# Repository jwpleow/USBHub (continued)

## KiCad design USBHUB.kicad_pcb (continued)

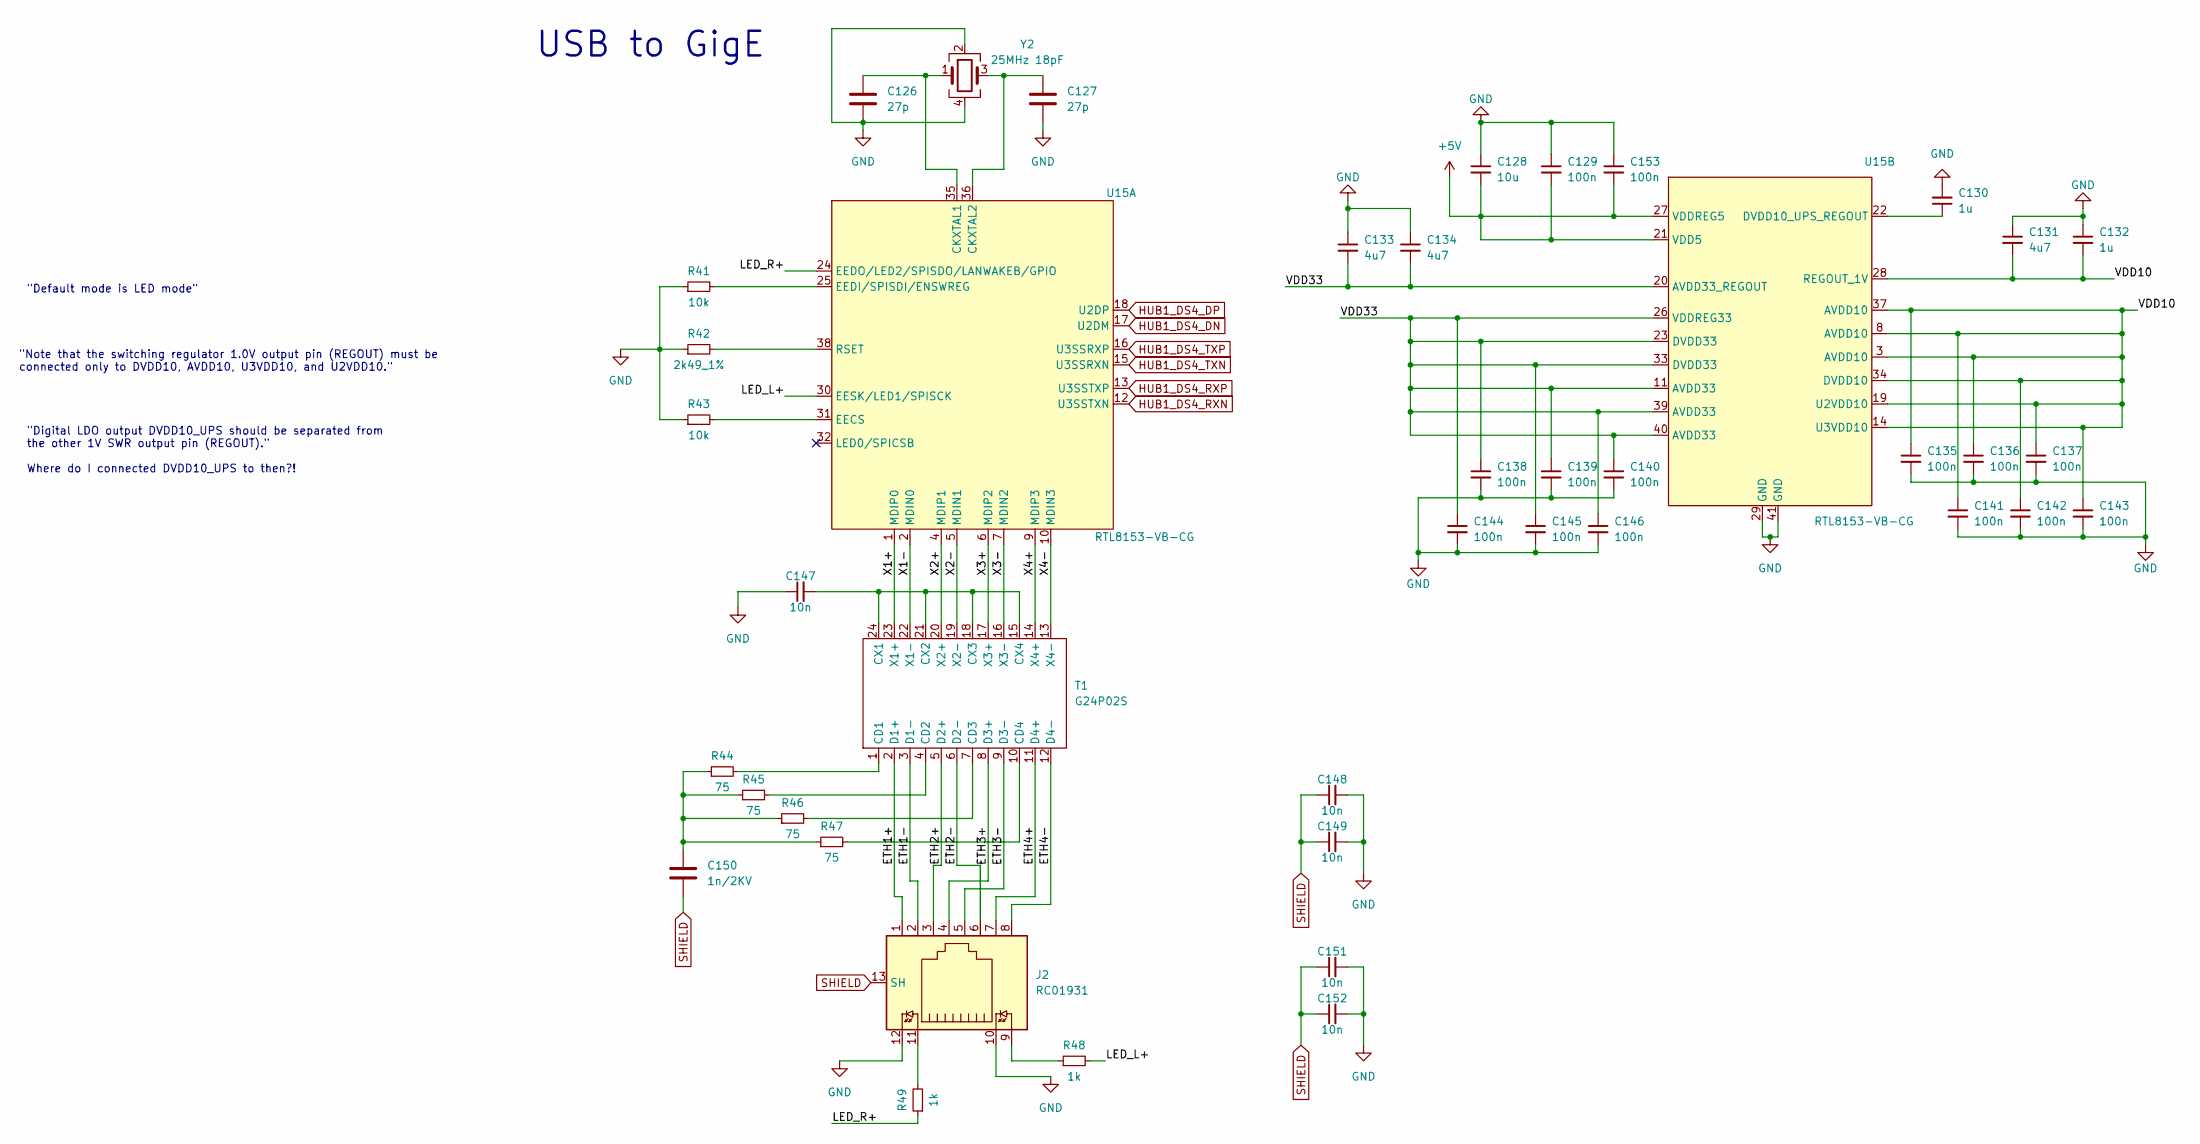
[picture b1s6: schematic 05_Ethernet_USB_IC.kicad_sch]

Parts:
C126, C127: 27p; C_0402_1005Metric
C128: 10u; C_0603_1608Metric
C129, C135, C136, C137, C138, C139, C140, C141, C142, C143, C144, C145, C146, C153: 100n; C_0402_1005Metric
C130, C132: 1u; C_0603_1608Metric
C131, C133, C134: 4u7; C_0603_1608Metric
C147, C148, C149, C151, C152: 10n; C_0402_1005Metric
C150: 1n/2KV; C_1206_3216Metric
J2: RC01931
R41, R43: 10k; R_0402_1005Metric
R42: 2k49_1%; R_0603_1608Metric
R44, R45, R46, R47: 75; R_0603_1608Metric
R48, R49: 1k; R_0603_1608Metric
T1: G24P02S
U15: RTL8153-VB-CG; RTL8153B-VB-CG
Y2: 25MHz 18pF; Crystal_SMD_2016-4Pin_2.0x1.6mm

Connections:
+5V: C128.2, C129.2, C153.2, U15.21 (VDD5), U15.27 (VDDREG5); also elsewhere on the board
/05 Ethernet USB IC/ETH1+: J2.1, T1.2 (D1+)
/05 Ethernet USB IC/ETH1-: J2.2, T1.3 (D1-)
/05 Ethernet USB IC/ETH2+: J2.3, T1.5 (D2+)
/05 Ethernet USB IC/ETH2-: J2.6, T1.6 (D2-)
/05 Ethernet USB IC/ETH3+: J2.4, T1.8 (D3+)
/05 Ethernet USB IC/ETH3-: J2.5, T1.9 (D3-)
/05 Ethernet USB IC/ETH4+: J2.7, T1.11 (D4+)
/05 Ethernet USB IC/ETH4-: J2.8, T1.12 (D4-)
/05 Ethernet USB IC/LED_L+: R48.2, U15.30 (EESK/LED1/SPISCK)
/05 Ethernet USB IC/LED_R+: R49.1, U15.24 (EEDO/LED2/SPISDO/LANWAKEB/GPIO)
/05 Ethernet USB IC/VDD10: C131.2, C132.2, C135.1, C136.1, C137.1, C141.1, C142.1, C143.1, U15.3 (AVDD10), U15.8 (AVDD10), U15.14 (U3VDD10), U15.19 (U2VDD10), U15.28 (REGOUT_1V), U15.34 (DVDD10), U15.37 (AVDD10)
/05 Ethernet USB IC/VDD33: C133.2, C134.2, C138.1, C139.1, C140.1, C144.1, C145.1, C146.1, U15.11 (AVDD33), U15.20 (AVDD33_REGOUT), U15.23 (DVDD33), U15.26 (VDDREG33), U15.33 (DVDD33), U15.39 (AVDD33), U15.40 (AVDD33)
/05 Ethernet USB IC/X1+: T1.23 (X1+), U15.1 (MDIP0)
/05 Ethernet USB IC/X1-: T1.22 (X1-), U15.2 (MDIN0)
/05 Ethernet USB IC/X2+: T1.20 (X2+), U15.4 (MDIP1)
/05 Ethernet USB IC/X2-: T1.19 (X2-), U15.5 (MDIN1)
/05 Ethernet USB IC/X3+: T1.17 (X3+), U15.6 (MDIP2)
/05 Ethernet USB IC/X3-: T1.16 (X3-), U15.7 (MDIN2)
/05 Ethernet USB IC/X4+: T1.14 (X4+), U15.9 (MDIP3)
/05 Ethernet USB IC/X4-: T1.13 (X4-), U15.10 (MDIN3)
GND: C126.2, C127.2, C128.1, C129.1, C130.2, C131.1, C132.1, C133.1, C134.1, C135.2, C136.2, C137.2, C138.2, C139.2, C140.2, C141.2, C142.2, C143.2, C144.2, C145.2, C146.2, C147.1, C148.2, C149.2, C151.2, C152.2, C153.1, J2.10, J2.12, R41.1, R42.1, R43.1, U15.29 (GND), U15.41 (GND), Y2.2, Y2.4; also elsewhere on the board
HUB1_DS4_DN: U15.17 (U2DM); also elsewhere on the board
HUB1_DS4_DP: U15.18 (U2DP); also elsewhere on the board
HUB1_DS4_RXN: U15.12 (U3SSTXN); also elsewhere on the board
HUB1_DS4_RXP: U15.13 (U3SSTXP); also elsewhere on the board
HUB1_DS4_TXN: U15.15 (U3SSRXN); also elsewhere on the board
HUB1_DS4_TXP: U15.16 (U3SSRXP); also elsewhere on the board
unnamed: C150.1, R44.1, R45.1, R46.1, R47.1
unnamed: J2.9, R48.1
unnamed: J2.11, R49.2
unnamed: R44.2, T1.1 (CD1)
unnamed: R45.2, T1.4 (CD2)
unnamed: R46.2, T1.7 (CD3)
unnamed: R47.2, T1.10 (CD4)
unnamed: C147.2, T1.15 (CX4), T1.18 (CX3), T1.21 (CX2), T1.24 (CX1)
unnamed: C126.1, U15.35 (CKXTAL1), Y2.1
unnamed: C127.1, U15.36 (CKXTAL2), Y2.3
unnamed: R43.2, U15.31 (EECS)
unnamed: R41.2, U15.25 (EEDI/SPISDI/ENSWREG)
unnamed: R42.2, U15.38 (RSET)
unnamed: C130.1, U15.22 (DVDD10_UPS_REGOUT)
SHIELD: C148.1, C149.1, C150.2, C151.1, C152.1, J2.13 (SH)

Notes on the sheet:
"Note that the switching regulator 1.0V output pin (REGOUT) must be connected only to DVDD10, AVDD10, U3VDD10, and U2VDD10."
USB to GigE
"Digital LDO output DVDD10_UPS should be separated from the other 1V SWR output pin (REGOUT)." Where do I connected DVDD10_UPS to then?!
"Default mode is LED mode"

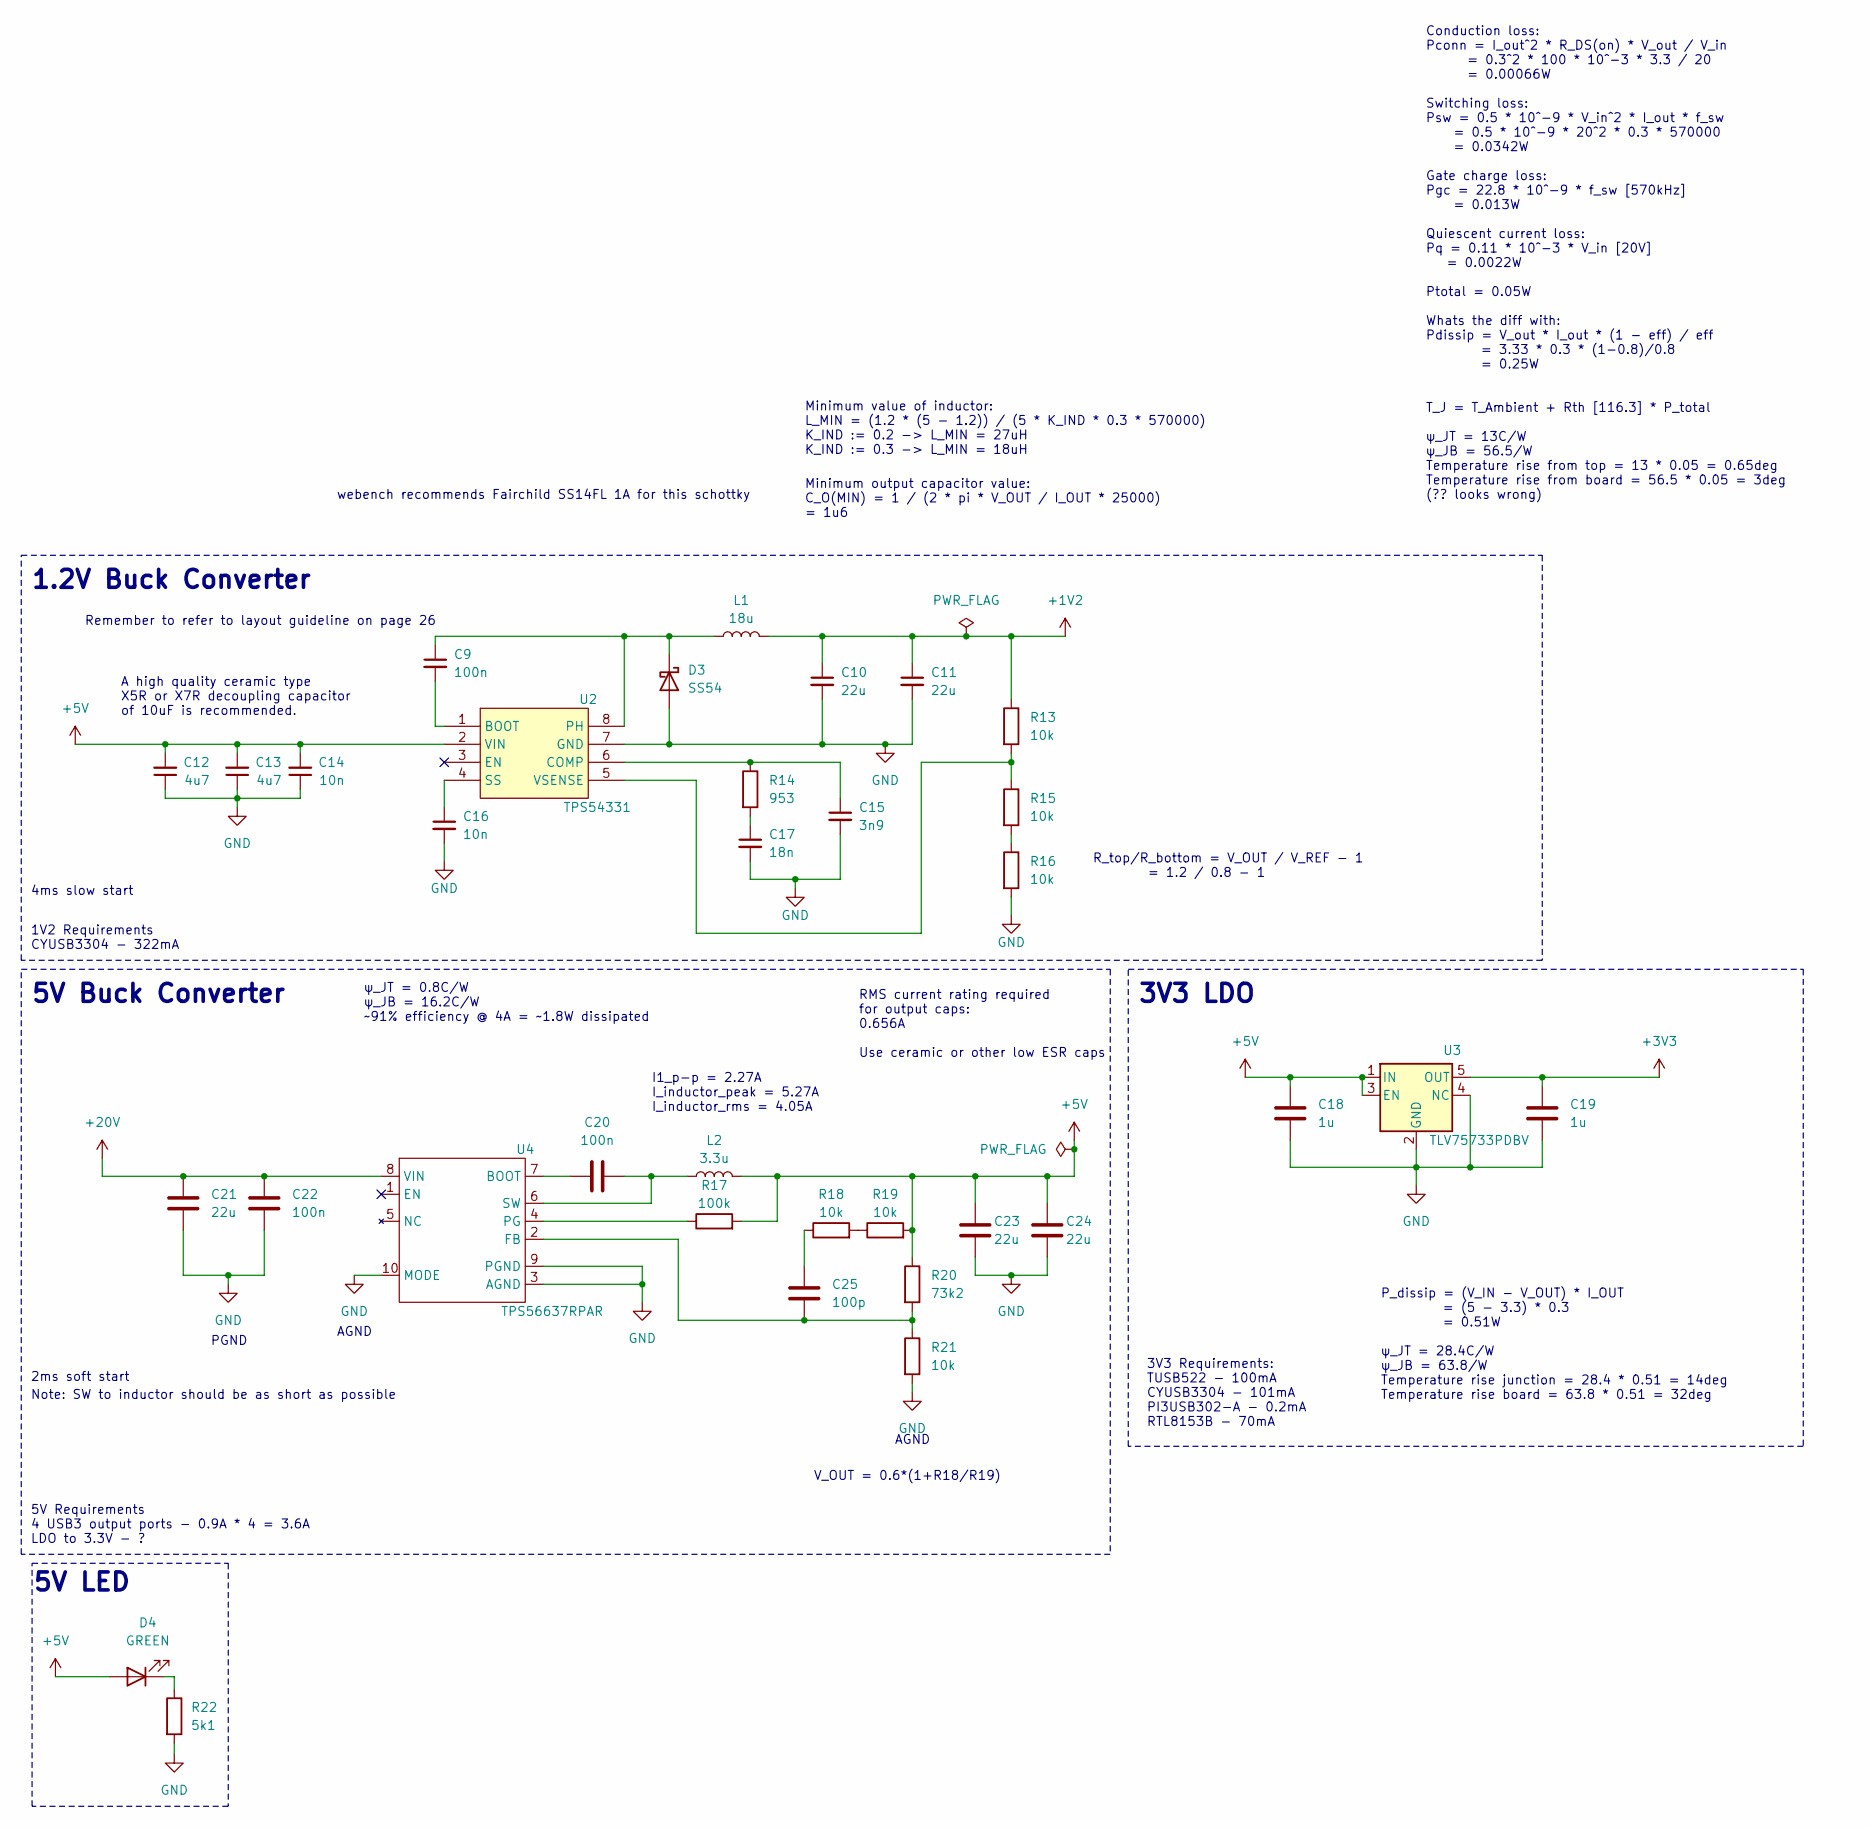
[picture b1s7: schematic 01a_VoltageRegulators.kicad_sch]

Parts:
C9, C20, C22: 100n; C_0603_1608Metric
C10, C11: 22u; C_0603_1608Metric
C12, C13: 4u7; C_0603_1608Metric
C14, C16: 10n; C_0603_1608Metric
C15: 3n9; C_0603_1608Metric
C17: 18n; C_0603_1608Metric
C18, C19: 1u; C_0603_1608Metric
C21, C23, C24: 22u; C_0805_2012Metric
C25: 100p; C_0603_1608Metric
D3: SS54; D_SMA
D4: GREEN; LED_0603_1608Metric
L1: 18u; FNR6045Sx
L2: 3.3u; FXL0630x
R13, R15, R16, R18, R19, R21: 10k; R_0402_1005Metric
R14: 953; R_0603_1608Metric
R17: 100k; R_0603_1608Metric
R20: 73k2; R_0402_1005Metric
R22: 5k1; R_0603_1608Metric
U2: TPS54331; TPS54331DR
U3: TLV75733PDBV; SOT-23-5
U4: TPS56637RPAR

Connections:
+1V2: C10.1, C11.1, L1.2, R13.1; also elsewhere on the board
+3V3: C19.1, U3.5 (OUT); also elsewhere on the board
+5V: C12.2, C13.2, C14.2, C18.1, C23.1, C24.1, D4.2 (A), L2.2, R17.2, R19.2, R20.1, U2.2 (VIN), U3.1 (IN), U3.3 (EN); also elsewhere on the board
+20V: C21.1, C22.1, U4.8 (VIN); also elsewhere on the board
GND: C10.2, C11.2, C12.1, C13.1, C14.1, C15.2, C16.2, C17.2, C18.2, C19.2, C21.2, C22.2, C23.2, C24.2, D3.2 (A), R16.2, R21.2, R22.2, U2.7 (GND), U3.2 (GND), U3.4 (NC), U4.3 (AGND), U4.9 (PGND), U4.10 (MODE); also elsewhere on the board
unnamed: C17.1, R14.2
unnamed: C25.1, R18.1
unnamed: C9.1, D3.1 (K), L1.1, U2.8 (PH)
unnamed: D4.1 (K), R22.1
unnamed: R15.2, R16.1
unnamed: R18.2, R19.1
unnamed: C9.2, U2.1 (BOOT)
unnamed: C15.1, R14.1, U2.6 (COMP)
unnamed: C16.1, U2.4 (SS)
unnamed: R13.2, R15.1, U2.5 (VSENSE)
unnamed: C20.1, U4.7 (BOOT)
unnamed: C25.2, R20.2, R21.1, U4.2 (FB)
unnamed: R17.1, U4.4 (PG)
unnamed: C20.2, L2.1, U4.6 (SW)

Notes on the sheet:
3V3 LDO
R_top/R_bottom = V_OUT / V_REF - 1 = 1.2 / 0.8 - 1
V_OUT = 0.6*(1+R18/R19)
5V Requirements 4 USB3 output ports - 0.9A * 4 = 3.6A LDO to 3.3V - ?
AGND
5V LED
2ms soft start
4ms slow start
Note: SW to inductor should be as short as possible
3V3 Requirements: TUSB522 - 100mA CYUSB3304 - 101mA PI3USB302−A - 0.2mA RTL8153B - 70mA
RMS current rating required for output caps: 0.656A Use ceramic or other low ESR caps
Remember to refer to layout guideline on page 26
I1_p-p = 2.27A I_inductor_peak = 5.27A I_inductor_rms = 4.05A
1V2 Requirements CYUSB3304 - 322mA
A high quality ceramic type X5R or X7R decoupling capacitor of 10uF is recommended.
P_dissip = (V_IN - V_OUT) * I_OUT = (5 - 3.3) * 0.3 = 0.51W ψ_JT = 28.4C/W ψ_JB = 63.8/W Temperature rise junction = 28.4 * 0.51 = 14deg Temperature rise board = 63.8 * 0.51 = 32deg
5V Buck Converter
Minimum output capacitor value: C_O(MIN) = 1 / (2 * pi * V_OUT / I_OUT * 25000) = 1u6
webench recommends Fairchild SS14FL 1A for this schottky
Minimum value of inductor: L_MIN = (1.2 * (5 - 1.2)) / (5 * K_IND * 0.3 * 570000) K_IND := 0.2 -> L_MIN = 27uH K_IND := 0.3 -> L_MIN = 18uH
1.2V Buck Converter
Conduction loss: Pconn = I_out^2 * R_DS(on) * V_out / V_in = 0.3^2 * 100 * 10^-3 * 3.3 / 20 = 0.00066W Switching loss: Psw = 0.5 * 10^-9 * V_in^2 * I_out * f_sw = 0.5 * 10^-9 * 20^2 * 0.3 * 570000 = 0.0342W Gate charge loss: Pgc = 22.8 * 10^-9 * f_sw [570kHz] = 0.013W Quiescent current loss: Pq = 0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
ψ_JT = 0.8C/W ψ_JB = 16.2C/W ~91% efficiency @ 4A = ~1.8W dissipated
PGND

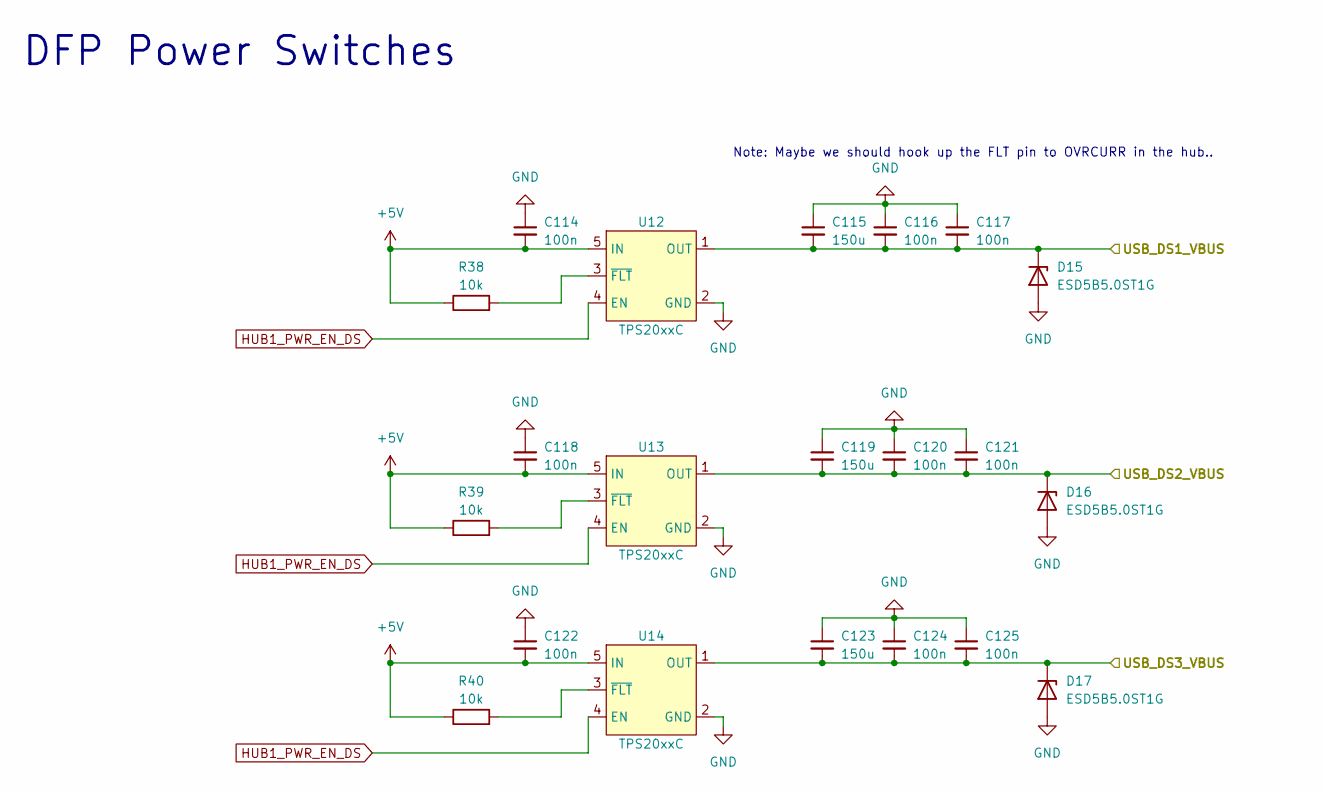
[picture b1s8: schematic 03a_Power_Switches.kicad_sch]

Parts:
C114, C116, C117, C118, C120, C121, C122, C124, C125: 100n; C_0603_1608Metric
C115, C119, C123: 150u; C_Elec_6.3x7.7
D15, D16, D17: ESD5B5.0ST1G; D_SOD-523
R38, R39, R40: 10k; R_0402_1005Metric
U12, U13, U14: TPS20xxC; SOT-23-5

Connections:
+5V: C114.2, C118.2, C122.2, R38.1, R39.1, R40.1, U12.5 (IN), U13.5 (IN), U14.5 (IN); also elsewhere on the board
/03 USB_DFP/USB_DS1_VBUS: C115.2, C116.2, C117.2, D15.1 (K), U12.1 (OUT); also elsewhere on the board
/03 USB_DFP/USB_DS2_VBUS: C119.2, C120.2, C121.2, D16.1 (K), U13.1 (OUT); also elsewhere on the board
/03 USB_DFP/USB_DS3_VBUS: C123.2, C124.2, C125.2, D17.1 (K), U14.1 (OUT); also elsewhere on the board
GND: C114.1, C115.1, C116.1, C117.1, C118.1, C119.1, C120.1, C121.1, C122.1, C123.1, C124.1, C125.1, D15.2 (A), D16.2 (A), D17.2 (A), U12.2 (GND), U13.2 (GND), U14.2 (GND); also elsewhere on the board
HUB1_PWR_EN_DS: U12.4 (EN), U13.4 (EN), U14.4 (EN); also elsewhere on the board
unnamed: R38.2, U12.3 (~FLT)
unnamed: R39.2, U13.3 (~FLT)
unnamed: R40.2, U14.3 (~FLT)

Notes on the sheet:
DFP Power Switches
Note: Maybe we should hook up the FLT pin to OVRCURR in the hub..

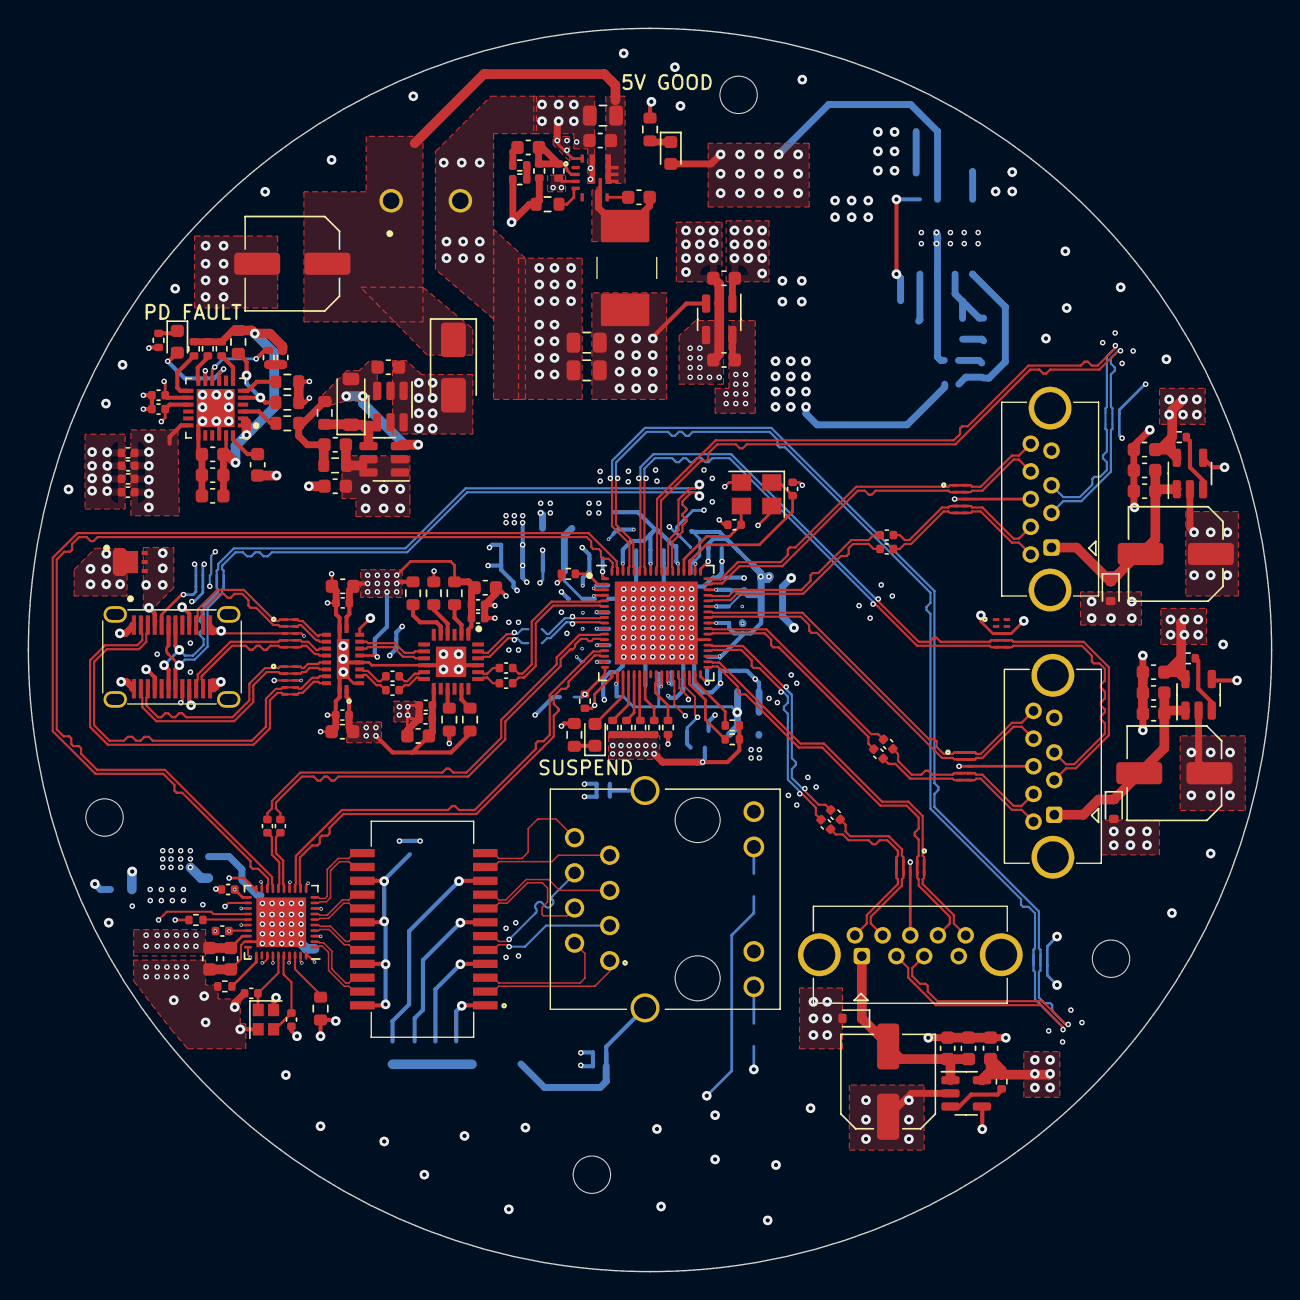
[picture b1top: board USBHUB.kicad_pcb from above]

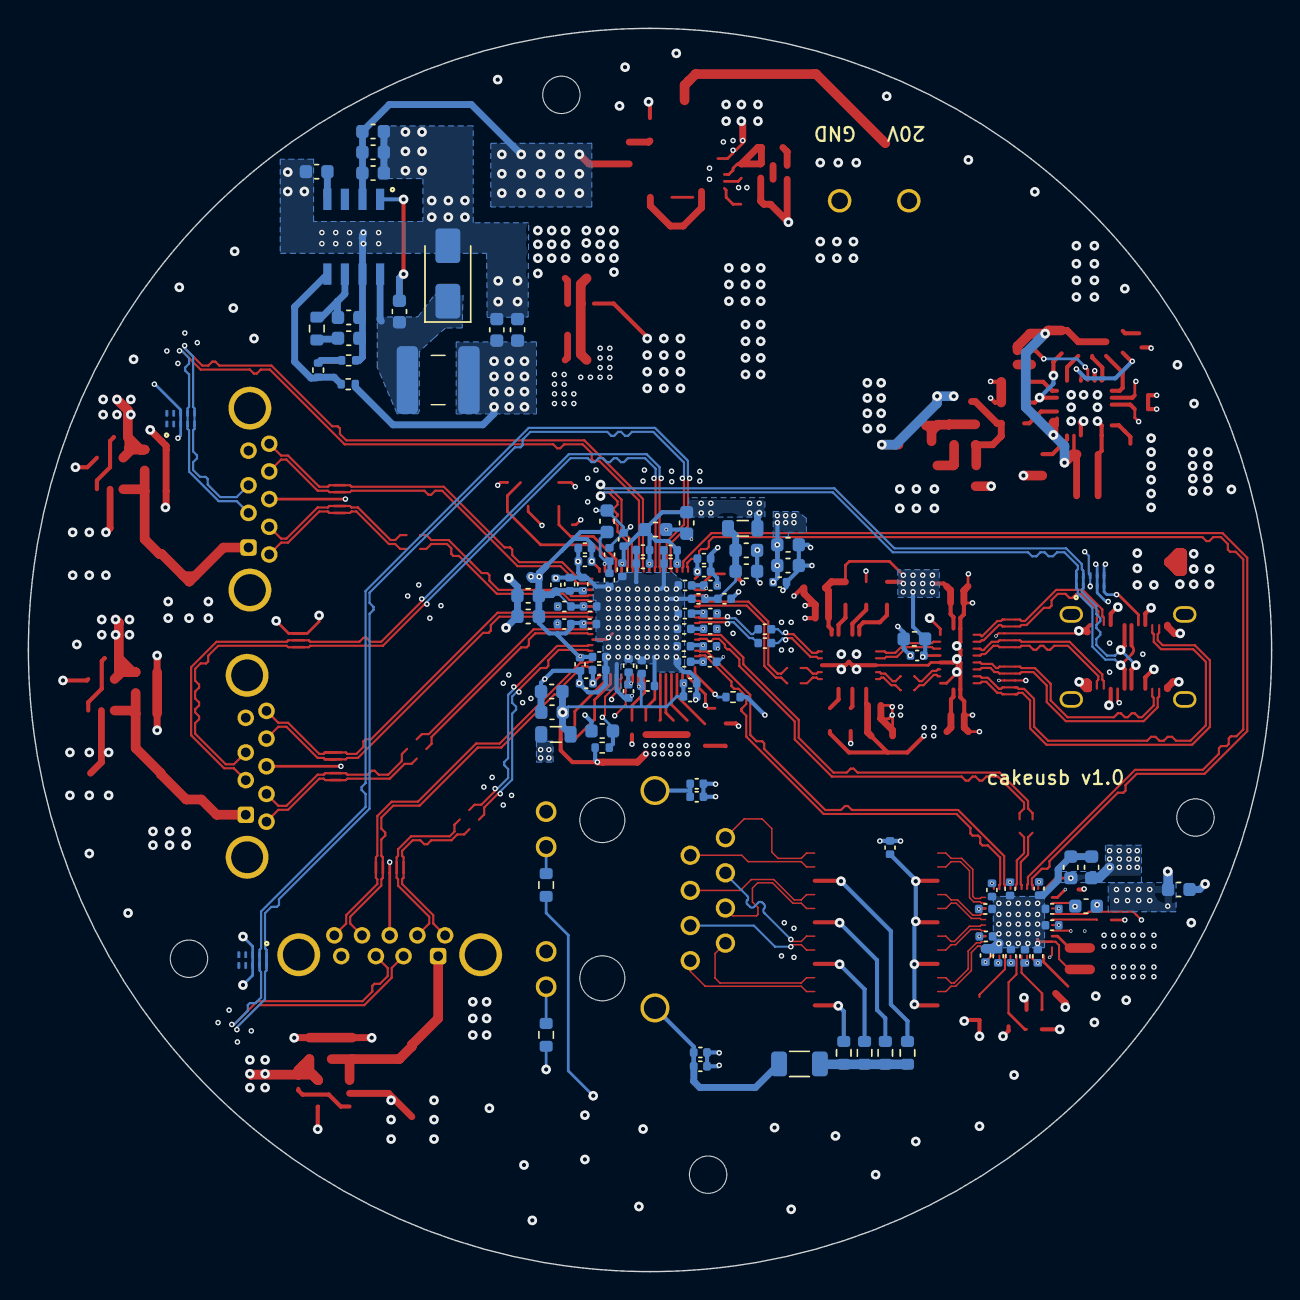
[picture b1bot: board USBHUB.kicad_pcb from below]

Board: 6 copper layers, 89.8 x 89.8 mm, 253 parts (109 on the bottom side), 156 nets.

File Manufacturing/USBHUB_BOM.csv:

"Designator","Qnty","Comment","Cmp name","Footprint","Description","JLCPCB Part #"
"C1, C115, C119, C123","4","150u","C_Small","Capacitor_SMD:C_Elec_6.3x7.7","Unpolarized capacitor, small symbol","C3032176"
"C2, C3, C5, C7, C18, C19, C53, C57, C73, C87, C100, C106, C130, C132","14","1u","C_Small","0603","Unpolarized capacitor, small symbol","C15849"
"C4","1","3u3","C_Small","0603","Unpolarized capacitor, small symbol","C5360803"
"C6, C8, C9, C20, C22, C114, C116, C117, C118, C120, C121, C122, C124, C125","14","100n","C_Small","0603","Unpolarized capacitor, small symbol","C30926"
"C10, C11, C52, C72, C86, C99, C105, C113","8","22u","C","0603","Unpolarized capacitor","C59461"
"C12, C13, C131, C133, C134","5","4u7","C_Small","0603","Unpolarized capacitor, small symbol","C19666"
"C14, C16","2","10n","C_Small","0603","Unpolarized capacitor, small symbol","C57112"
"C15","1","3n9","C_Small","0603","Unpolarized capacitor, small symbol","C2169349"
"C17","1","18n","C_Small","0603","Unpolarized capacitor, small symbol","C519551"
"C21, C23, C24","3","22u","C","0805","Unpolarized capacitor","C45783"
"C25","1","100p","C","0603","Unpolarized capacitor","C14858"
"C26, C27, C28, C29, C58, C60, C62, C64, C66, C68, C75, C77, C79, C81, C89, C91, C93, C95, C97, C102, C104, C108, C110, C112, C147, C148, C149, C151, C152","29","10n","C_Small","0402","Unpolarized capacitor, small symbol","C15195"
"C30, C31","2","220pF","C_Small","0402","Unpolarized capacitor, small symbol","C1530"
"C32, C35, C38, C39, C40, C128","6","10u","C_Small","0603","Unpolarized capacitor, small symbol","C19702"
"C33, C34, C36, C37, C41, C42, C43, C44, C45, C46, C47, C48, C49, C54, C55, C56, C59, C70, C71, C74, C76, C78, C80, C82, C83, C84, C85, C88, C101, C103, C107, C109, C111, C129, C135, C136, C137, C138, C139, C140, C141, C142, C143, C144, C145, C146, C153","47","100n","C_Small","0402","Unpolari capacitor, small symbol","C1525"
"C50, C51","2","10p","C","0402","Unpolarized capacitor","C32949"
"C61, C63, C65, C67, C69, C90, C92, C94, C96, C98","10","1n","C_Small","0402","Unpolarized capacitor, small symbol","C1523"
"C126, C127","2","27p","C","0402","Unpolarized capacitor","C1557"
"C150","1","1n/2KV","C","1206","Unpolarized capacitor","C9196"
"D1","1","BZT52C12","D_Zener","Diode_SMD:D_SOD-123","Zener diode","C2932744"
"D2, D14","2","RED","LED","0603","Light emitting diode","C2286"
"D3, D18","1","SS54","D_Schottky","Diode_SMD:D_SMA","40V 5A Schottky Barrier Rectifier Diode, SMA","C7420369"
"D4","1","GREEN","LED","0603","Light emitting diode","C2297"
"D5, D6, D7, D8, D9, D10, D11, D12, D13","9","PUSB3FR4Z","PUSB3FR4Z","PUSB3FR4Z","","C503418"
"D15, D16, D17","3","ESD5B5.0ST1G","D_Zener","Diode_SMD:D_SOD-523","Zener diode","C93623"
"FB1, FB2","2","BLM21PG221SN1D","FerriteBead_Small","0805","Ferrite bead, small symbol","C85840"
"J1","1","USB_C_Receptacle","USB_C_Receptacle","USB_C_Receptacle_GT-USB-7028x","","C963223"
"J2","1","RC01931","RC01931","RC01931","Ethernet RJ45, Vertical","C708651"
"J3","1","Screw_Terminal_01x02","Screw_Terminal_01x02","TerminalBlock_WJ103-5.0-2P","Generic screw terminal, single row, 01x02, script genera (kicad-library-utils/schlib/autogen/connector/)","C8439"
"L1","1","18u","L","FNR6045Sx","Inductor","C168079"
"L2","1","3.3u","L","FXL0630x","Inductor","C167219"
"Q1, Q2","2","SI3421DV","SI3421DV","Package_TO_SOT_SMD:SOT-23-6","P-MOSFET transistor, gate/source/drain","C144884"
"R1","1","10k","R","0603","Resistor","C25804"
"R2","1","50k","R","0603","Resistor","C304067"
"R3, R5, R6, R7, R13, R15, R16, R18, R19, R21, R30, R31, R32, R33, R34, R38, R39, R40, R41, R43","20","10k","R_Small","0402","Resistor","C25744"
"R4, R24, R25, R26, R27, R48, R49","7","1k","R","0603","Resistor","C25744"
"R8, R9, R35, R36","4","2k","R","0402","Resistor","C4109"
"R10, R11, R12, R22, R23, R37","6","5k1","R","0603","Resistor","C23186"
"R14","1","953","R","0603","Resistor","C311896"
"R17","1","100k","R","0603","Resistor","C25803"
"R20","1","73k2","R","0402","Resistor","C185398"
"R28","1","200_1%","R","0402","Resistor","C25087"
"R29","1","6k04_1%","R","0402","Resistor","C25913"
"R42","1","2k49_1%","R_Small","0603","Resistor","C22908"
"R44, R45, R46, R47","4","75","R_Small","0603","Resistor","C4275"
"R50, R51","2","10k","R_Small","0402","Resistor","C25744"
"T1","1","G24P02S","G24P02S","G24P02S","RJ45 100/1000 Base-T SMT Transformer","C2827276"
"U1","1","CYPD3177_24x","CYPD3177_24x","CYPD3177_24LQx_QFN-24_EP_4x4_Pitch0.5mm","USB Type-C PD Port Controller for Power Sinks","C2959321"
"U2","1","TPS54331","TPS54331DR","TPS54331DR","3.5 to 28-V Input, 3A Step Down Buck Converter 570kHz","C9865"
"U3","1","TLV75733PDBV","TLV75733PDBV","Package_TO_SOT_SMD:SOT-23-5","1A Low IQ Small Size Low Dropout Voltage Regulator, Fixed Output 3. SOT-23-5","C485517"
"U4","1","TPS56637RPAR","TPS56637RPAR","TPS56637RPAR","","C841386"
"U5","1","TVS2200DRVx","TVS2200DRVx","TVS2200DRVx","","C523793"
"U6","1","PI3USB302-Ax","PI3USB302-Ax","PI3USB302-Ax","3.3V, USB 3.0, 1-Port, 2:1 Mux/DeMux Switch","C500787"
"U7","1","TUSB522Px","TUSB522Px","TUSB522Px","3.3 V Dual-Channel USB 3.1 GEN 1 Redriver, Equalizer","C2675181"
"U8, U9, U10","3","USB_3_Type_A_Molex_484080003","USB_3_Type_A_Molex_484080003","Molex_484080003","","C587839"
"U11","1","CYUSB3304-68LTXx","CYUSB3304-68LTXx","CYUSB3304-68LTXx","","C914921"
"U12, U13, U14","3","TPS20xxC","TPS20xxC","Package_TO_SOT_SMD:SOT-23-5","","C181752"
"U15","1","RTL8153-VB-CG","RTL8153B-VB-CG","RTL8153B-VB-CG","","C2802072"
"Y1","1","26MHz","Crystal_GND24","Crystal:Crystal_SMD_3225-4Pin_3.2x2.5mm","Four pin crystal, GND on pins 2 and 4","C362346"
"Y2","1","25MHz 18pF","Crystal_GND24","Crystal:Crystal_SMD_2016-4Pin_2.0x1.6mm","Four pin crystal, GND on pins 2 and 4","C648942"

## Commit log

2024-01-14 update readme, WIP on PD
2024-01-16 more WIP on power delivery
2024-01-16 add gitignore and notes
2024-01-19 finish PD controller schematic
2024-01-19 update grid spacing
2024-01-19 fix warnings
2024-01-20 paste kicad symbols and libs directly in here
2024-01-21 start layout of usb PD
2024-01-21 Finish PCB design
2024-01-21 some touchups
2024-01-21 add manufacturing files
2024-01-22 update research notes
2024-01-23 Add ESD for usb parts research, add TUSB522P and PI3USB302
2024-01-24 Add ESD protection for UFP, create buck converter model
2024-01-25 more work on the power section
2024-01-26 add usb hub controller schematic, fix up redriver
2024-01-29 WIP hub and DFP
2024-01-31 use simpler buck for 5V
2024-02-01 finish up schematics and ERC
2024-02-01 update kicad syms
2024-02-02 finish setting footprints
2024-02-05 symbol fixes, switch ESD protection for USB datalines
2024-02-12 fix symbols, route UFP DPs and voltage regs
2024-02-17 add RTL8153
2024-02-19 route power delivery controller
2024-02-25 settle on a layout
2024-02-26 working on pcb
2024-02-28 power layout for ethernet usb nic
2024-03-04 add schottky for usb pd
2024-03-10 finish layout draft
2024-03-10 fixing drcs
2024-03-11 fix gnd plane splits
2024-03-13 finish bom list
2024-03-13 fix bom
